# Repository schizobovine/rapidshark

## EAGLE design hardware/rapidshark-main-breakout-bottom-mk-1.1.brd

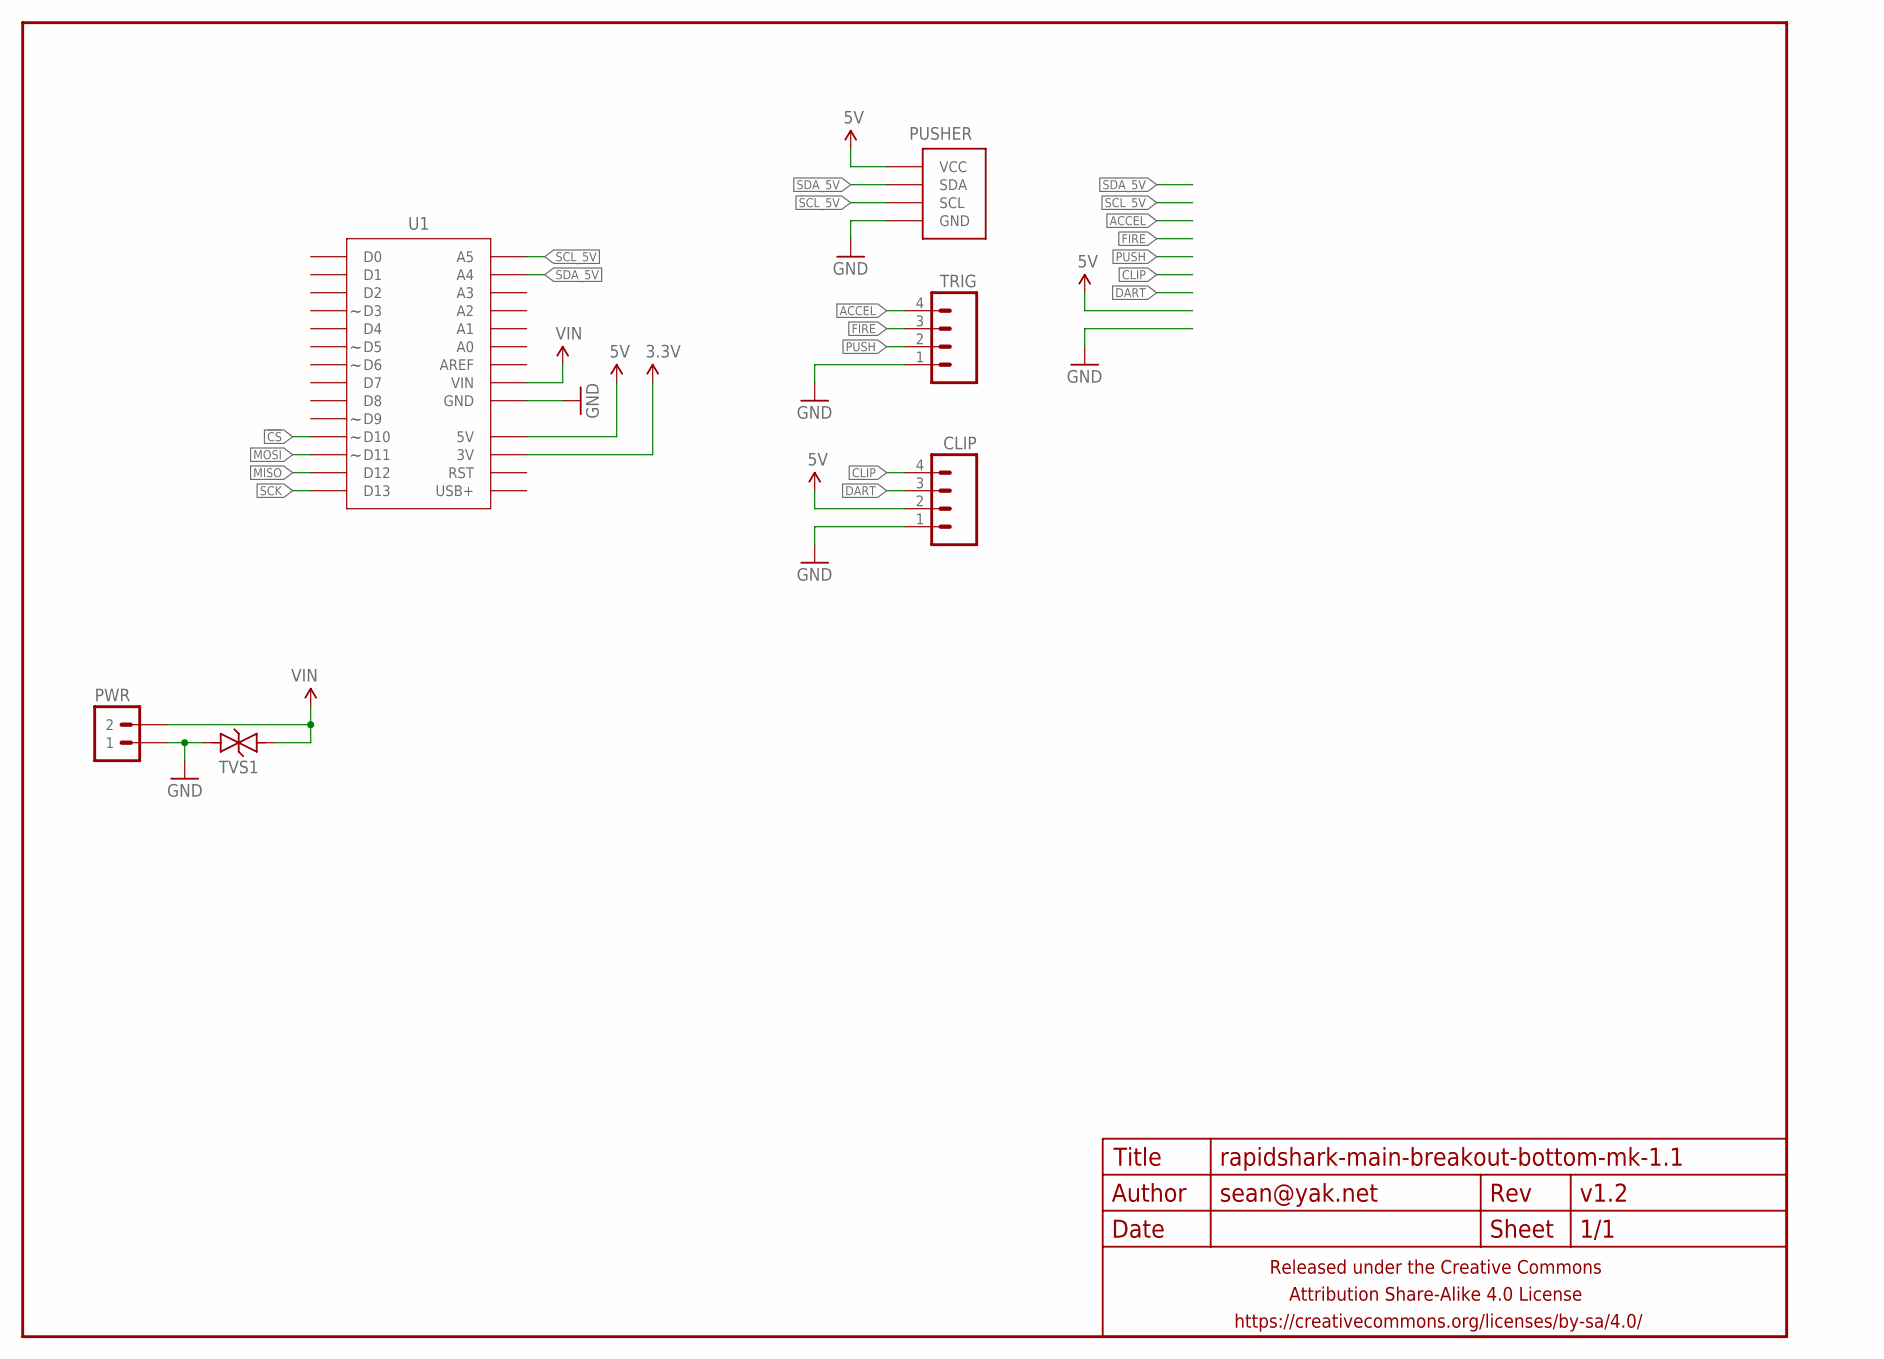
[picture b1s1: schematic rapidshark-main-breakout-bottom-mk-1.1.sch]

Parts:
CLIP: M04JST-PTH-VERT; JST-4-PH-VERT-PTH
FRAME1: FRAME-LETTERNO_PACKAGE; DUMMY
PUSHER: M04-I2CJST-4-PH-VERT-NS; JST-4-PH-VERT-PTH
PWR: M02PTH-CENTERED-R+; 1X02-CENTER-R+
TRIG: M04JST-PTH-VERT; JST-4-PH-VERT-PTH
TVS1: TVSDO-41-10.16MM; DO-41-TVS-BI-10.16MM
U1: ADAFRUIT_METRO_MININOHOLES-OUTSIDER; ADAFRUIT_METRO_MINI_OUTSIDER

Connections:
3.3V: U1.17 (3V)
5V: CLIP.2, PUSHER.2 (VCC), U1.18 (5V)
!CS: U1.11 (D10)
ACCEL: TRIG.4
CLIP: CLIP.4
DART: CLIP.3
FIRE: TRIG.3
GND: CLIP.1, PUSHER.1 (GND), PWR.1, TRIG.1, TVS1.P$1 (1), U1.19 (GND), U1.20 (GND)
MISO: U1.13 (D12)
MOSI: U1.12 (D11)
PUSH: TRIG.2
SCK: U1.14 (D13)
SCL_5V: PUSHER.4 (SCL), U1.28 (A5)
SDA_5V: PUSHER.3 (SDA), U1.27 (A4)
VIN: PWR.2, TVS1.P$2 (2), U1.21 (VIN)

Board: 2 copper layers, 7 parts (2 on the bottom side), 5 nets, no tracks yet.

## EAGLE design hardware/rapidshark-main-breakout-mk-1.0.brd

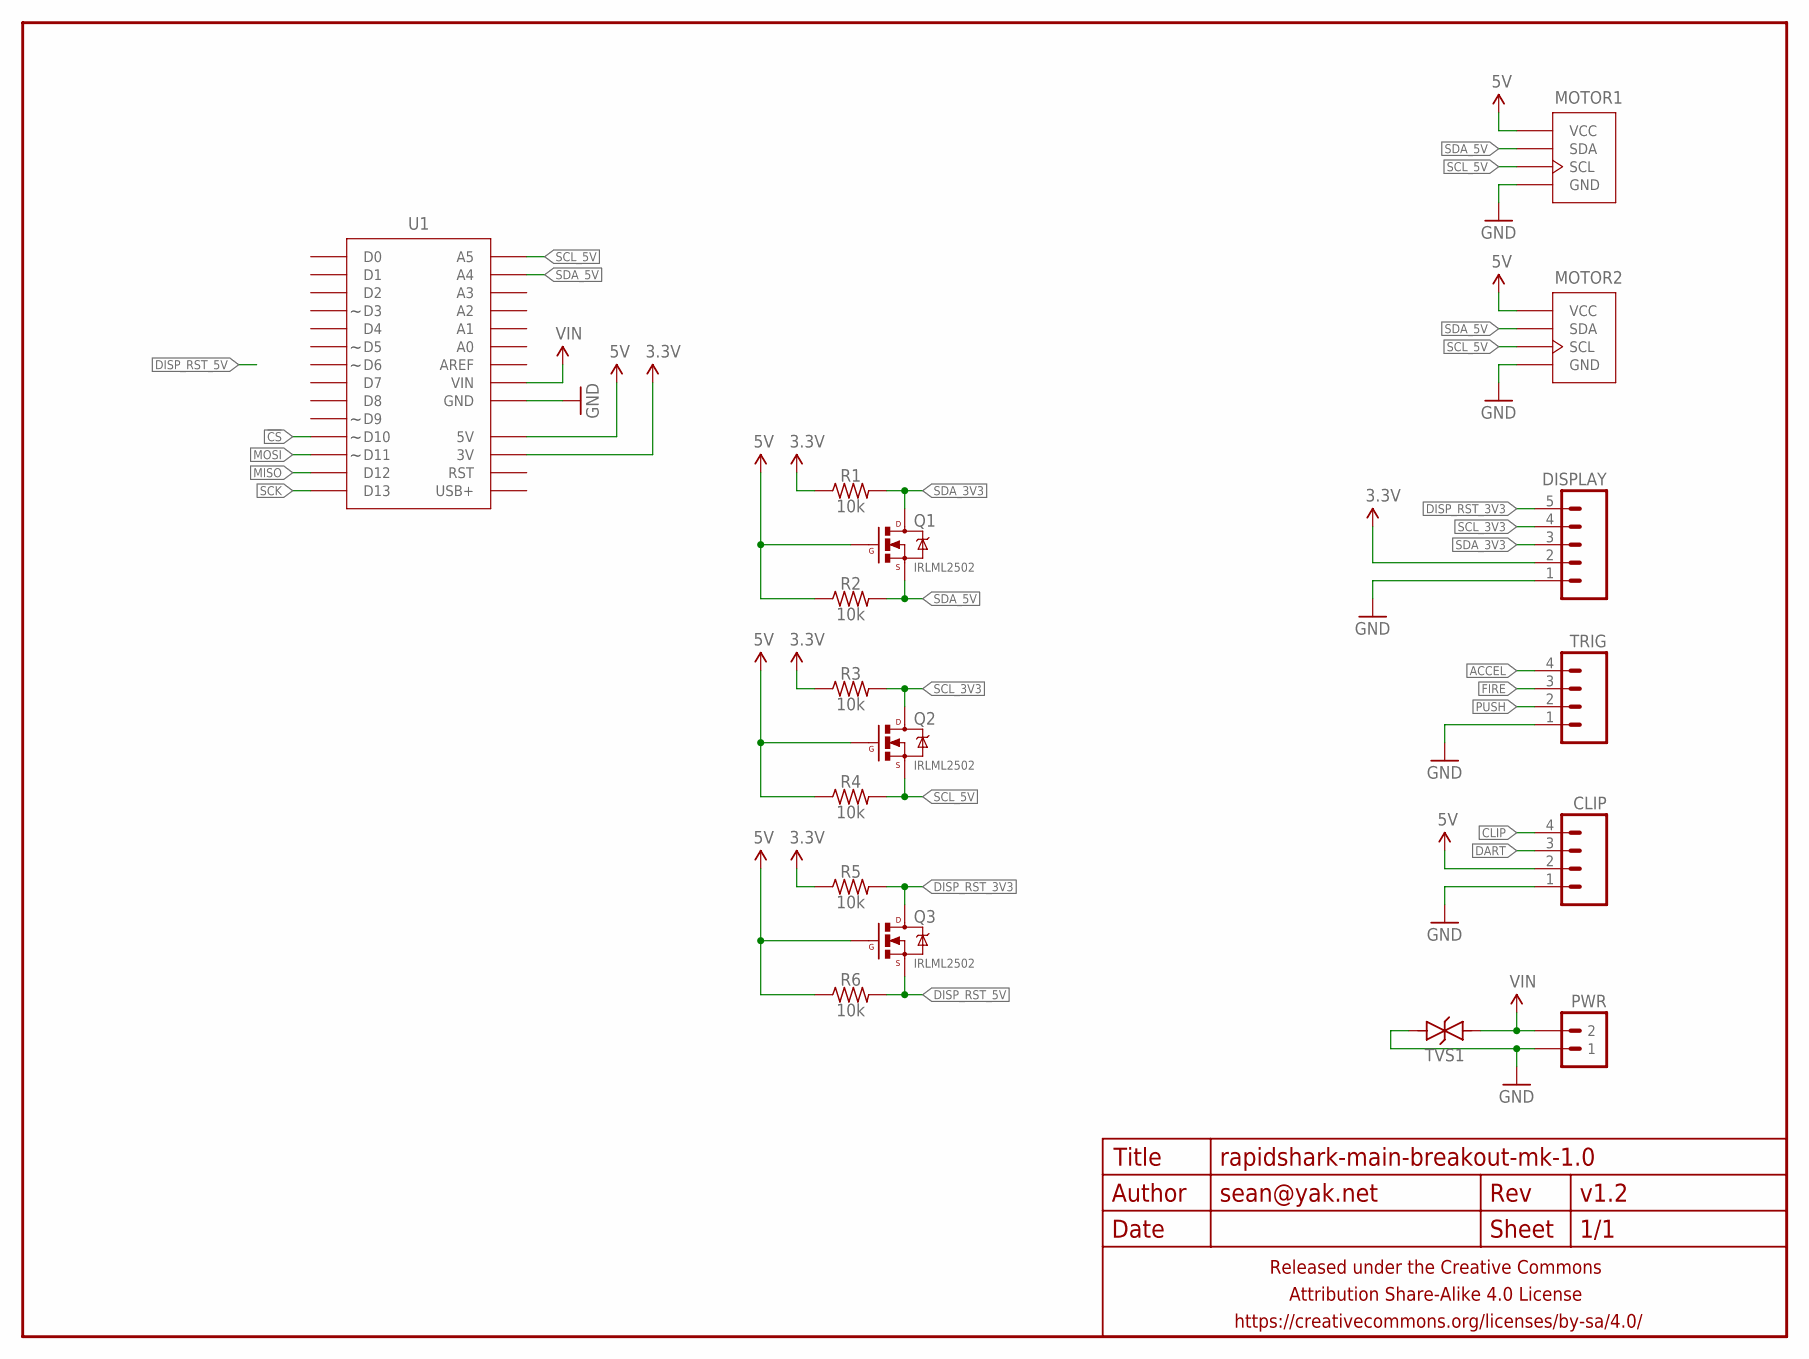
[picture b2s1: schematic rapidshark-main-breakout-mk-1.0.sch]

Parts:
CLIP: M04JST-PTH-VERT; JST-4-PH-VERT-PTH
DISPLAY: M05JST-PH-VERT-PTH; JST-5-PH-VERT-PTH
FRAME1: FRAME-LETTERNO_PACKAGE; DUMMY
MOTOR1, MOTOR2: M04-I2CJST-4-PH-VERT-NS; JST-4-PH-VERT-PTH
PWR: M02PTH-CENTERED-R+; 1X02-CENTER-R+
Q1, Q2, Q3: IRLML2502; SOT23
R1, R2, R3, R4, R5, R6: 10k; R0603
TRIG: M04JST-PTH-VERT; JST-4-PH-VERT-PTH
TVS1: TVSSMA; SMA-DIODE-TVS-BIDIR
U1: ADAFRUIT_METRO_MINISMD-NOHOLES; ADAFRUIT_METRO_MINI_SMD

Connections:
3.3V: DISPLAY.2, R1.1, R3.1, R5.1, U1.17 (3V)
5V: CLIP.2, MOTOR1.2 (VCC), MOTOR2.2 (VCC), Q1.1 (G), Q2.1 (G), Q3.1 (G), R2.1, R4.1, R6.1, U1.18 (5V)
!CS: U1.11 (D10)
ACCEL: TRIG.4
CLIP: CLIP.4
DART: CLIP.3
DISP_RST_3V3: DISPLAY.5, Q3.3 (D), R5.2
DISP_RST_5V: Q3.2 (S), R6.2
FIRE: TRIG.3
GND: CLIP.1, DISPLAY.1, MOTOR1.1 (GND), MOTOR2.1 (GND), PWR.1, TRIG.1, TVS1.2, U1.19 (GND), U1.20 (GND)
MISO: U1.13 (D12)
MOSI: U1.12 (D11)
PUSH: TRIG.2
SCK: U1.14 (D13)
SCL_3V3: DISPLAY.4, Q2.3 (D), R3.2
SCL_5V: MOTOR1.4 (SCL), MOTOR2.4 (SCL), Q2.2 (S), R4.2, U1.28 (A5)
SDA_3V3: DISPLAY.3, Q1.3 (D), R1.2
SDA_5V: MOTOR1.3 (SDA), MOTOR2.3 (SDA), Q1.2 (S), R2.2, U1.27 (A4)
VIN: PWR.2, TVS1.1, U1.21 (VIN)

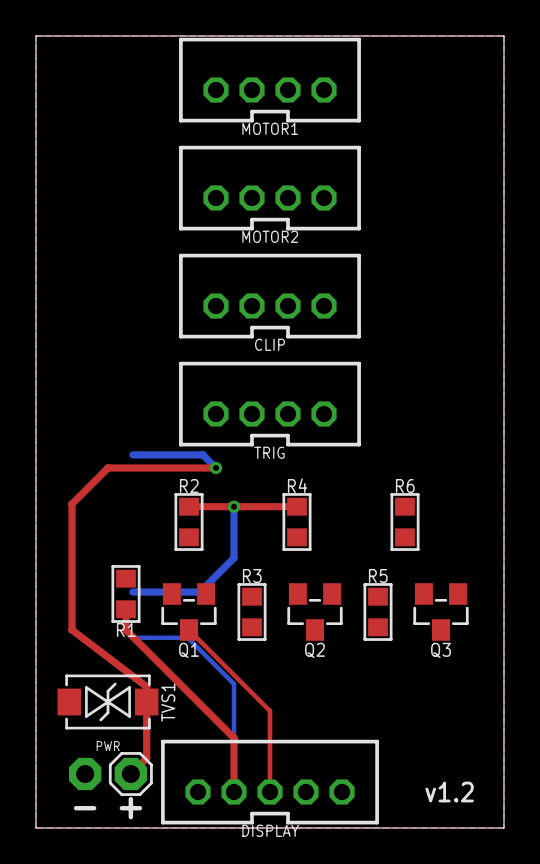
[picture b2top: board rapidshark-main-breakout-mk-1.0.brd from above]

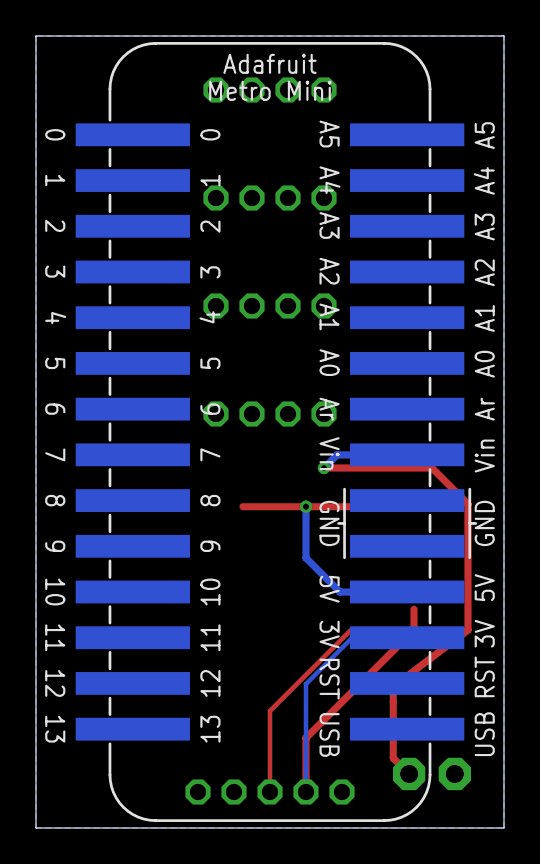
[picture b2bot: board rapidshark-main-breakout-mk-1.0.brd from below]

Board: 2 copper layers, 26.0 x 44.0 mm, 18 parts (2 on the bottom side), 10 nets.

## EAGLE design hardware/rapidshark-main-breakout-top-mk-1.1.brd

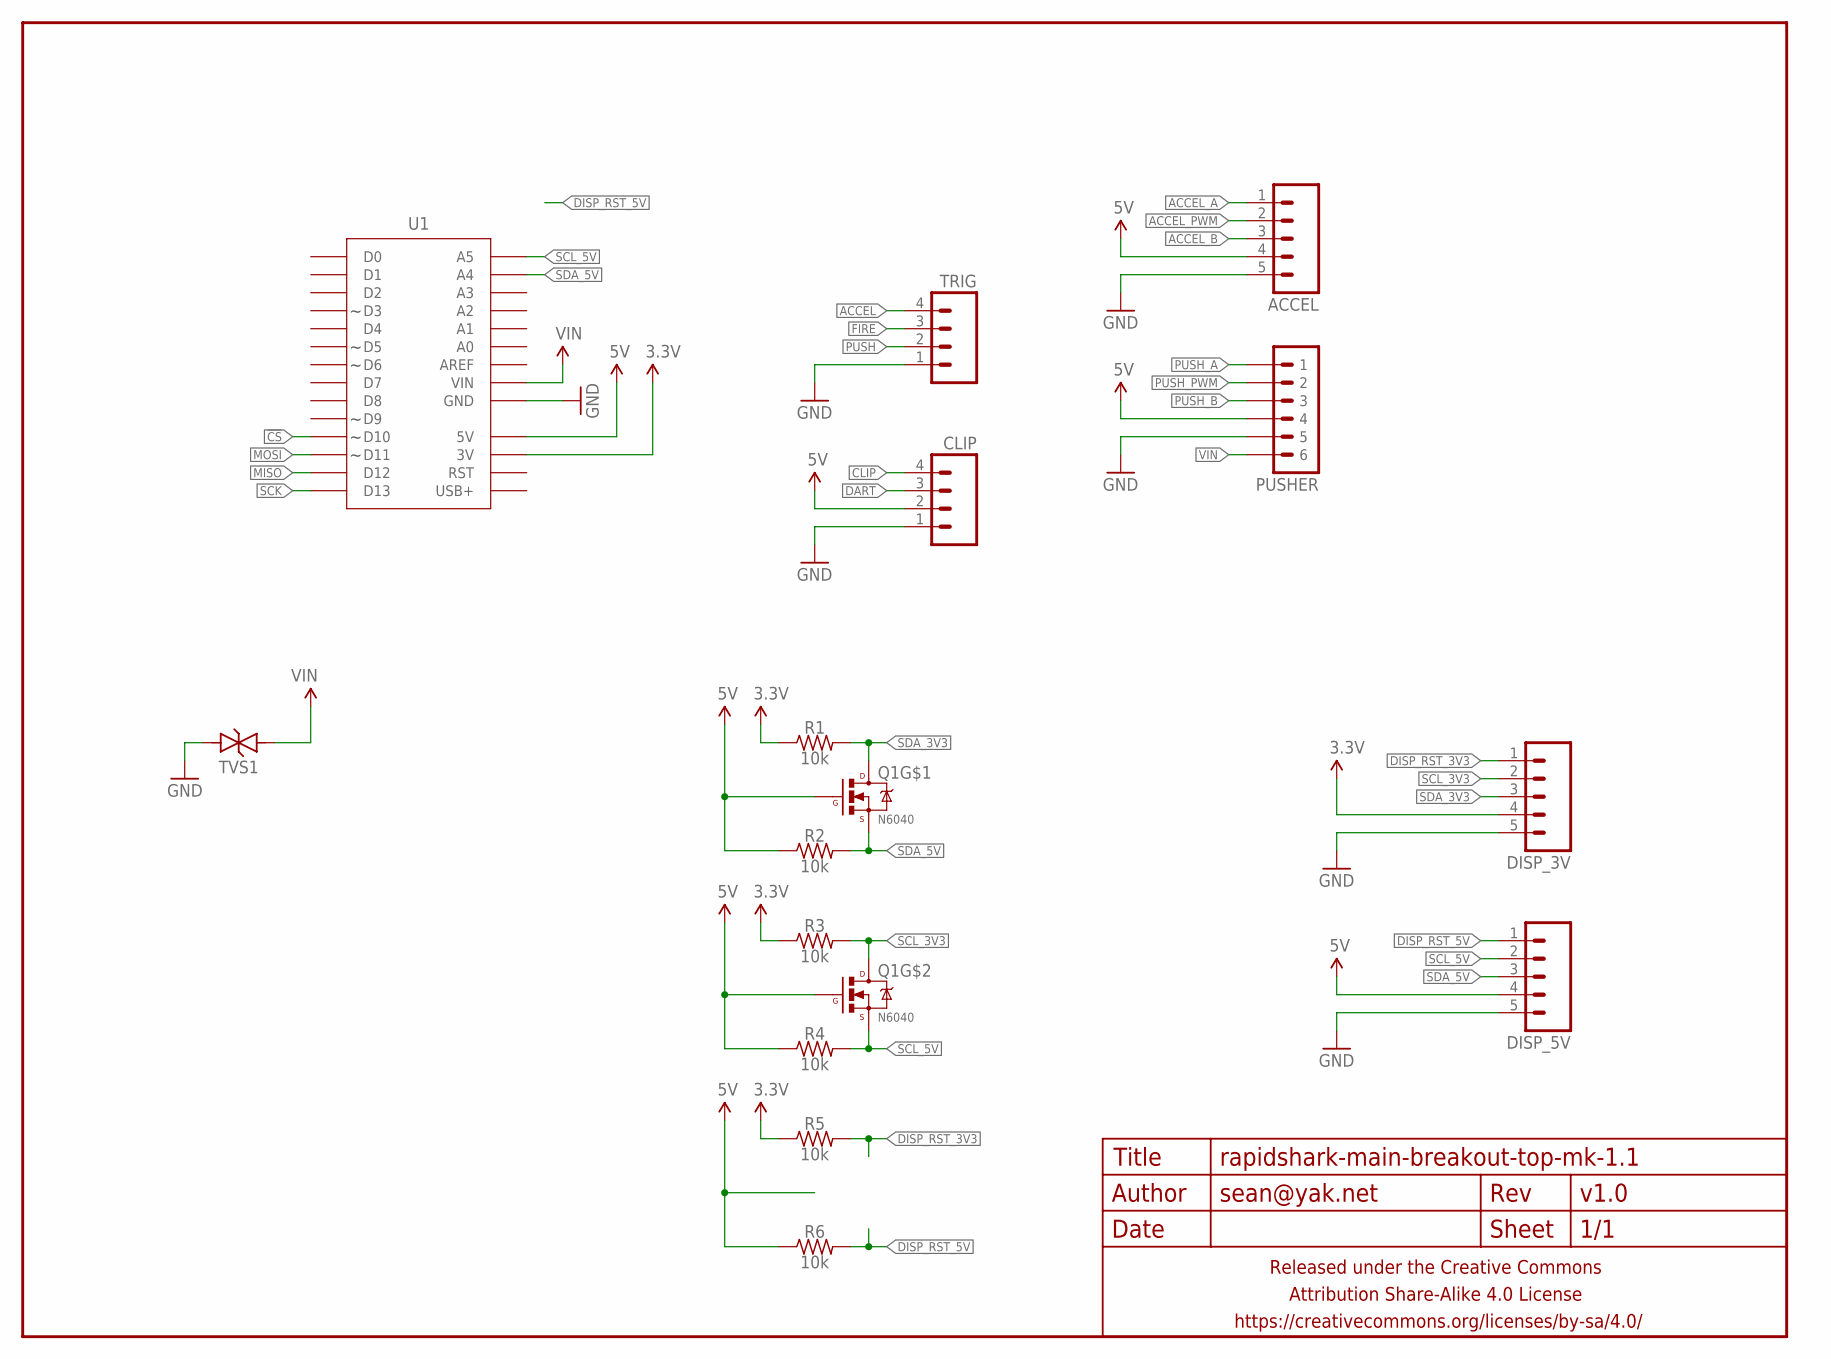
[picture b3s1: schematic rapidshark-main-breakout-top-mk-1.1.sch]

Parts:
ACCEL: M05JST-PH-VERT-PTH; JST-5-PH-VERT-PTH
CLIP: M04JST-PTH-VERT; JST-4-PH-VERT-PTH
DISP_3V, DISP_5V: M05JST-PH-VERT-PTH; JST-5-PH-VERT-PTH
FRAME1: FRAME-LETTERNO_PACKAGE; DUMMY
PUSHER: M06JST-PH-PTH-VERT; JST-6-PH-VERT-PTH
Q1: N6040; SO08
R1, R2, R3, R4, R5, R6: 10k; R0603
TRIG: M04JST-PTH-VERT; JST-4-PH-VERT-PTH
TVS1: TVSSMA; SMA-DIODE-TVS-BIDIR
U1: ADAFRUIT_METRO_MININOSILK-ABMBI; ADAFRUIT_METRO_MINI_FLIPPED

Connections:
3.3V: DISP_3V.4, R1.1, R3.1, R5.1, U1.17 (3V)
5V: ACCEL.4, CLIP.2, DISP_5V.4, Q1.2 (G), Q1.4 (G), R2.1, R4.1, R6.1, U1.18 (5V)
!CS: U1.11 (D10)
ACCEL: TRIG.4
ACCEL_A: ACCEL.1
ACCEL_B: ACCEL.3
ACCEL_PWM: ACCEL.2
CLIP: CLIP.4
DART: CLIP.3
DISP_RST_3V3: DISP_3V.1, R5.2
DISP_RST_5V: DISP_5V.1, R6.2
FIRE: TRIG.3
GND: ACCEL.5, CLIP.1, DISP_3V.5, DISP_5V.5, TRIG.1, TVS1.1, U1.19 (GND), U1.20 (GND)
MISO: U1.13 (D12)
MOSI: U1.12 (D11)
PUSH: TRIG.2
PUSH_A: PUSHER.1
PUSH_B: PUSHER.3
PUSH_PWM: PUSHER.2
SCK: U1.14 (D13)
SCL_3V3: DISP_3V.2, Q1.5 (D), Q1.6 (D), R3.2
SCL_5V: DISP_5V.2, Q1.3 (S), R4.2, U1.28 (A5)
SDA_3V3: DISP_3V.3, Q1.7 (D), Q1.8 (D), R1.2
SDA_5V: DISP_5V.3, Q1.1 (S), R2.2, U1.27 (A4)
VIN: PUSHER.6, TVS1.2, U1.21 (VIN)

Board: 2 copper layers, 16 parts (1 on the bottom side), 10 nets, no tracks yet.

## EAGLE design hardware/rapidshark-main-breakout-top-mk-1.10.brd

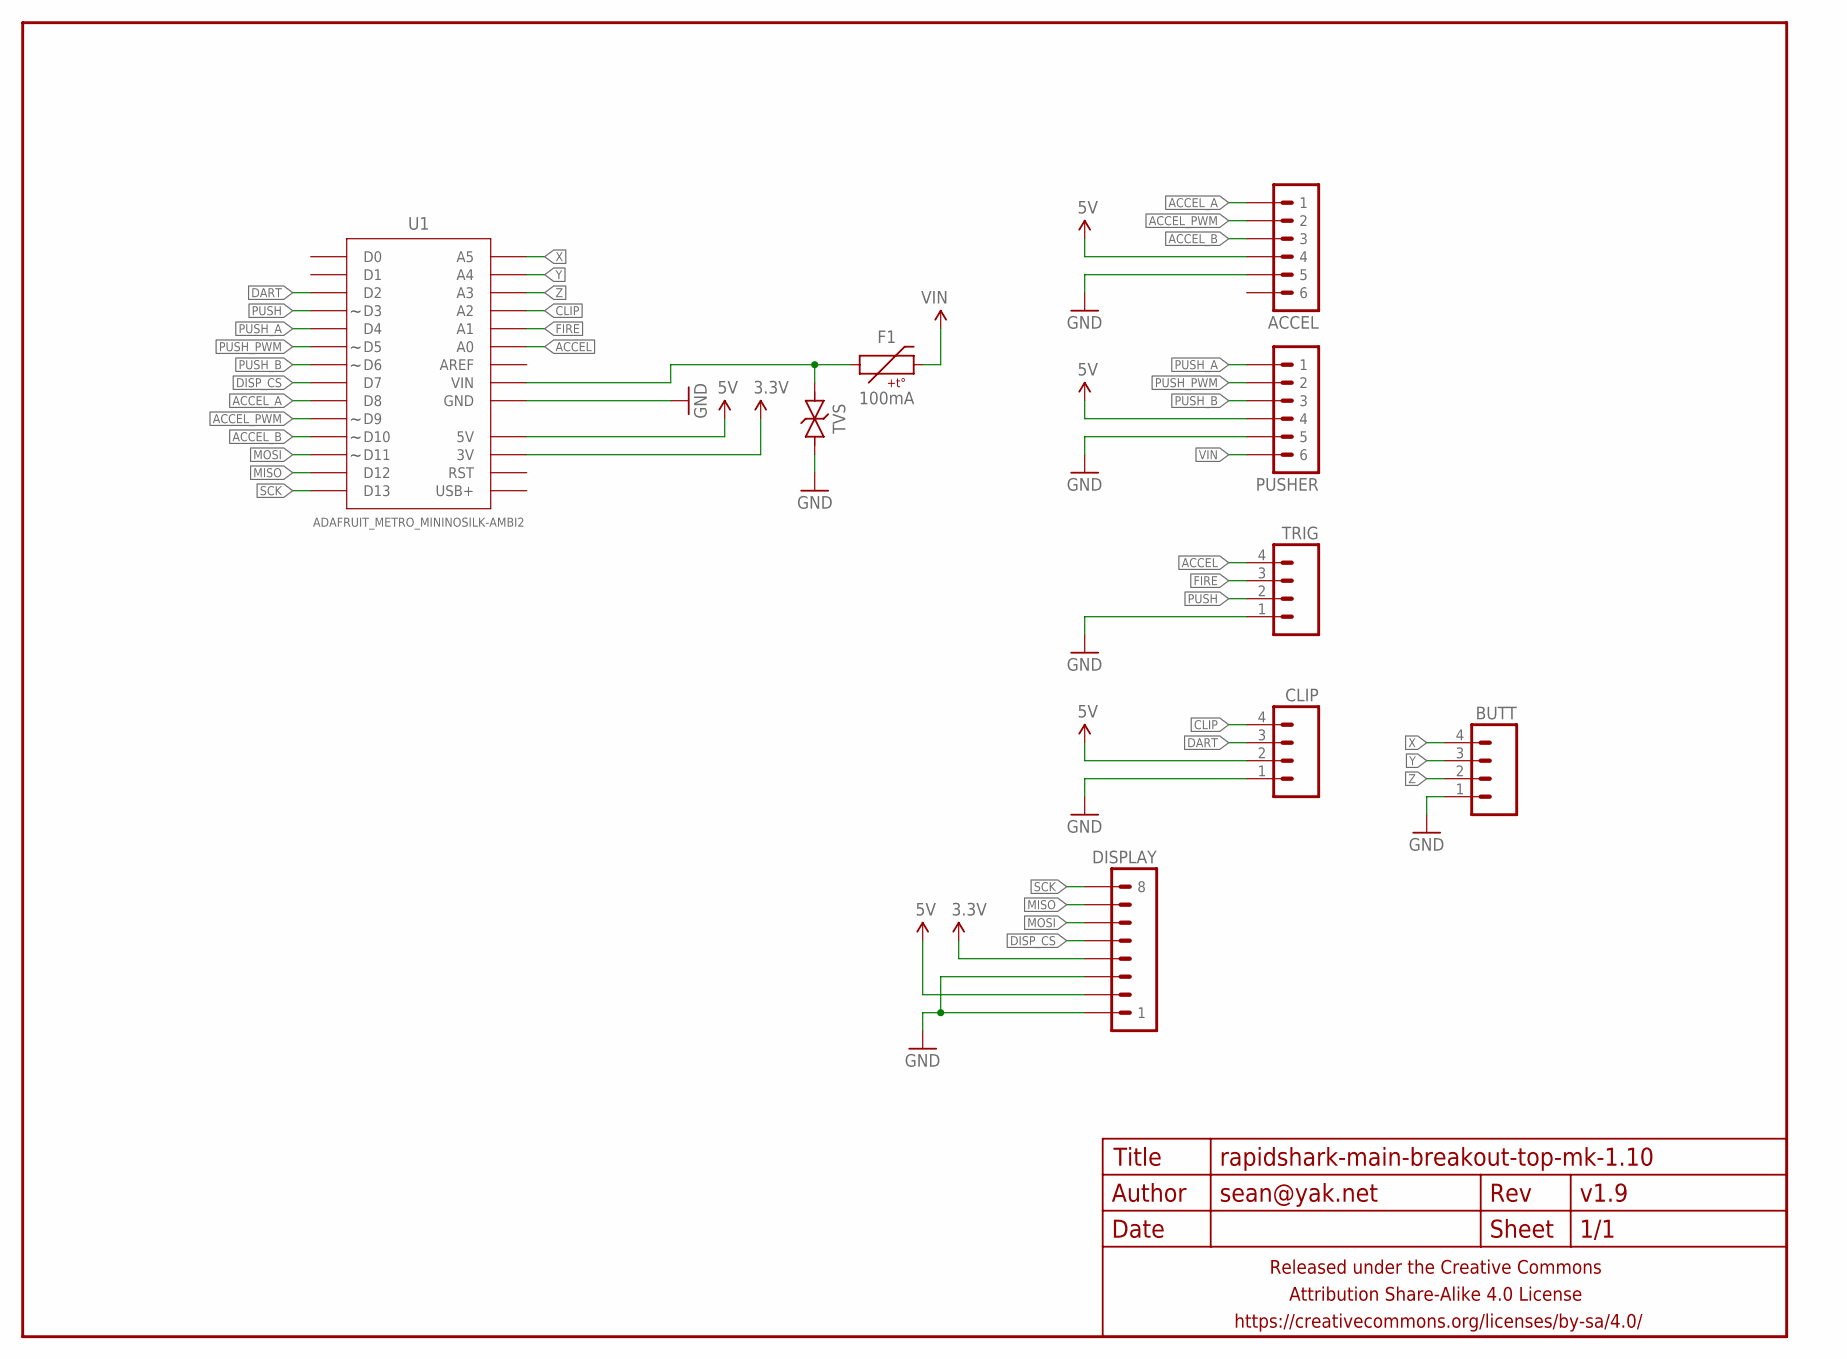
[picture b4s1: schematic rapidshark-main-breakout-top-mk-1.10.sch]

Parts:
ACCEL: M06JST-PH-PTH-VERT; JST-6-PH-VERT-PTH
BUTT: M04JST-PTH-VERT; JST-4-PH-VERT-PTH
CLIP: M04JST-PTH-VERT; JST-4-PH-VERT-PTH
DISPLAY: M08JST-PH-VERT-PTH; JST-8-VERT-PTH
F1: 100mA; PTC-1206
FRAME1: FRAME-LETTERNO_PACKAGE; DUMMY
PUSHER: M06JST-PH-PTH-VERT; JST-6-PH-VERT-PTH
TRIG: M04JST-PTH-VERT; JST-4-PH-VERT-PTH
TVS: TVSSMA; SMA-DIODE-TVS-BIDIR
U1: ADAFRUIT_METRO_MININOSILK-AMBI2; ADAFRUIT_METRO_MINI_BACK

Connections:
3.3V: DISPLAY.4, U1.17 (3V)
5V: ACCEL.4, CLIP.2, DISPLAY.2, PUSHER.4, U1.18 (5V)
ACCEL: TRIG.4, U1.23 (A0)
ACCEL_A: ACCEL.1, U1.9 (D8)
ACCEL_B: ACCEL.3, U1.11 (D10)
ACCEL_PWM: ACCEL.2, U1.10 (D9)
CLIP: CLIP.4, U1.25 (A2)
DART: CLIP.3, U1.3 (D2)
DISP_CS: DISPLAY.5, U1.8 (D7)
FIRE: TRIG.3, U1.24 (A1)
GND: ACCEL.5, BUTT.1, CLIP.1, DISPLAY.1, DISPLAY.3, PUSHER.5, TRIG.1, TVS.1, U1.19 (GND), U1.20 (GND)
MISO: DISPLAY.7, U1.13 (D12)
MOSI: DISPLAY.6, U1.12 (D11)
unnamed: F1.1, TVS.2, U1.21 (VIN)
PUSH: TRIG.2, U1.4 (D3)
PUSH_A: PUSHER.1, U1.5 (D4)
PUSH_B: PUSHER.3, U1.7 (D6)
PUSH_PWM: PUSHER.2, U1.6 (D5)
SCK: DISPLAY.8, U1.14 (D13)
VIN: F1.2, PUSHER.6
X: BUTT.4, U1.28 (A5)
Y: BUTT.3, U1.27 (A4)
Z: BUTT.2, U1.26 (A3)

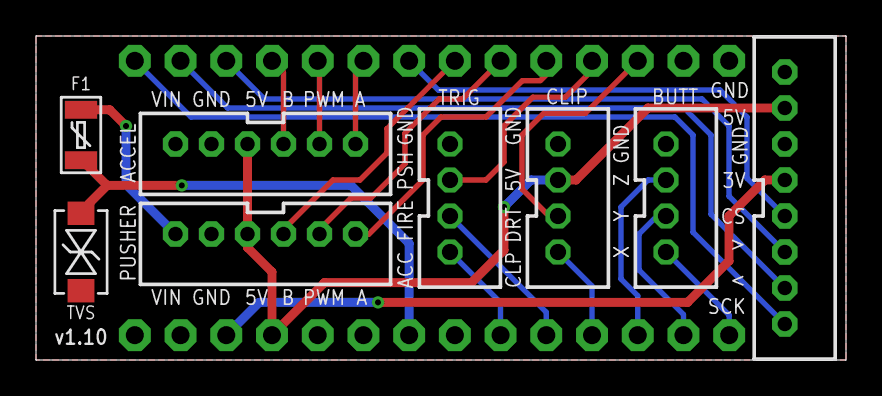
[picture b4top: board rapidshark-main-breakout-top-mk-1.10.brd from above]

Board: 2 copper layers, 45.0 x 18.0 mm, 10 parts (1 on the bottom side), 23 nets.

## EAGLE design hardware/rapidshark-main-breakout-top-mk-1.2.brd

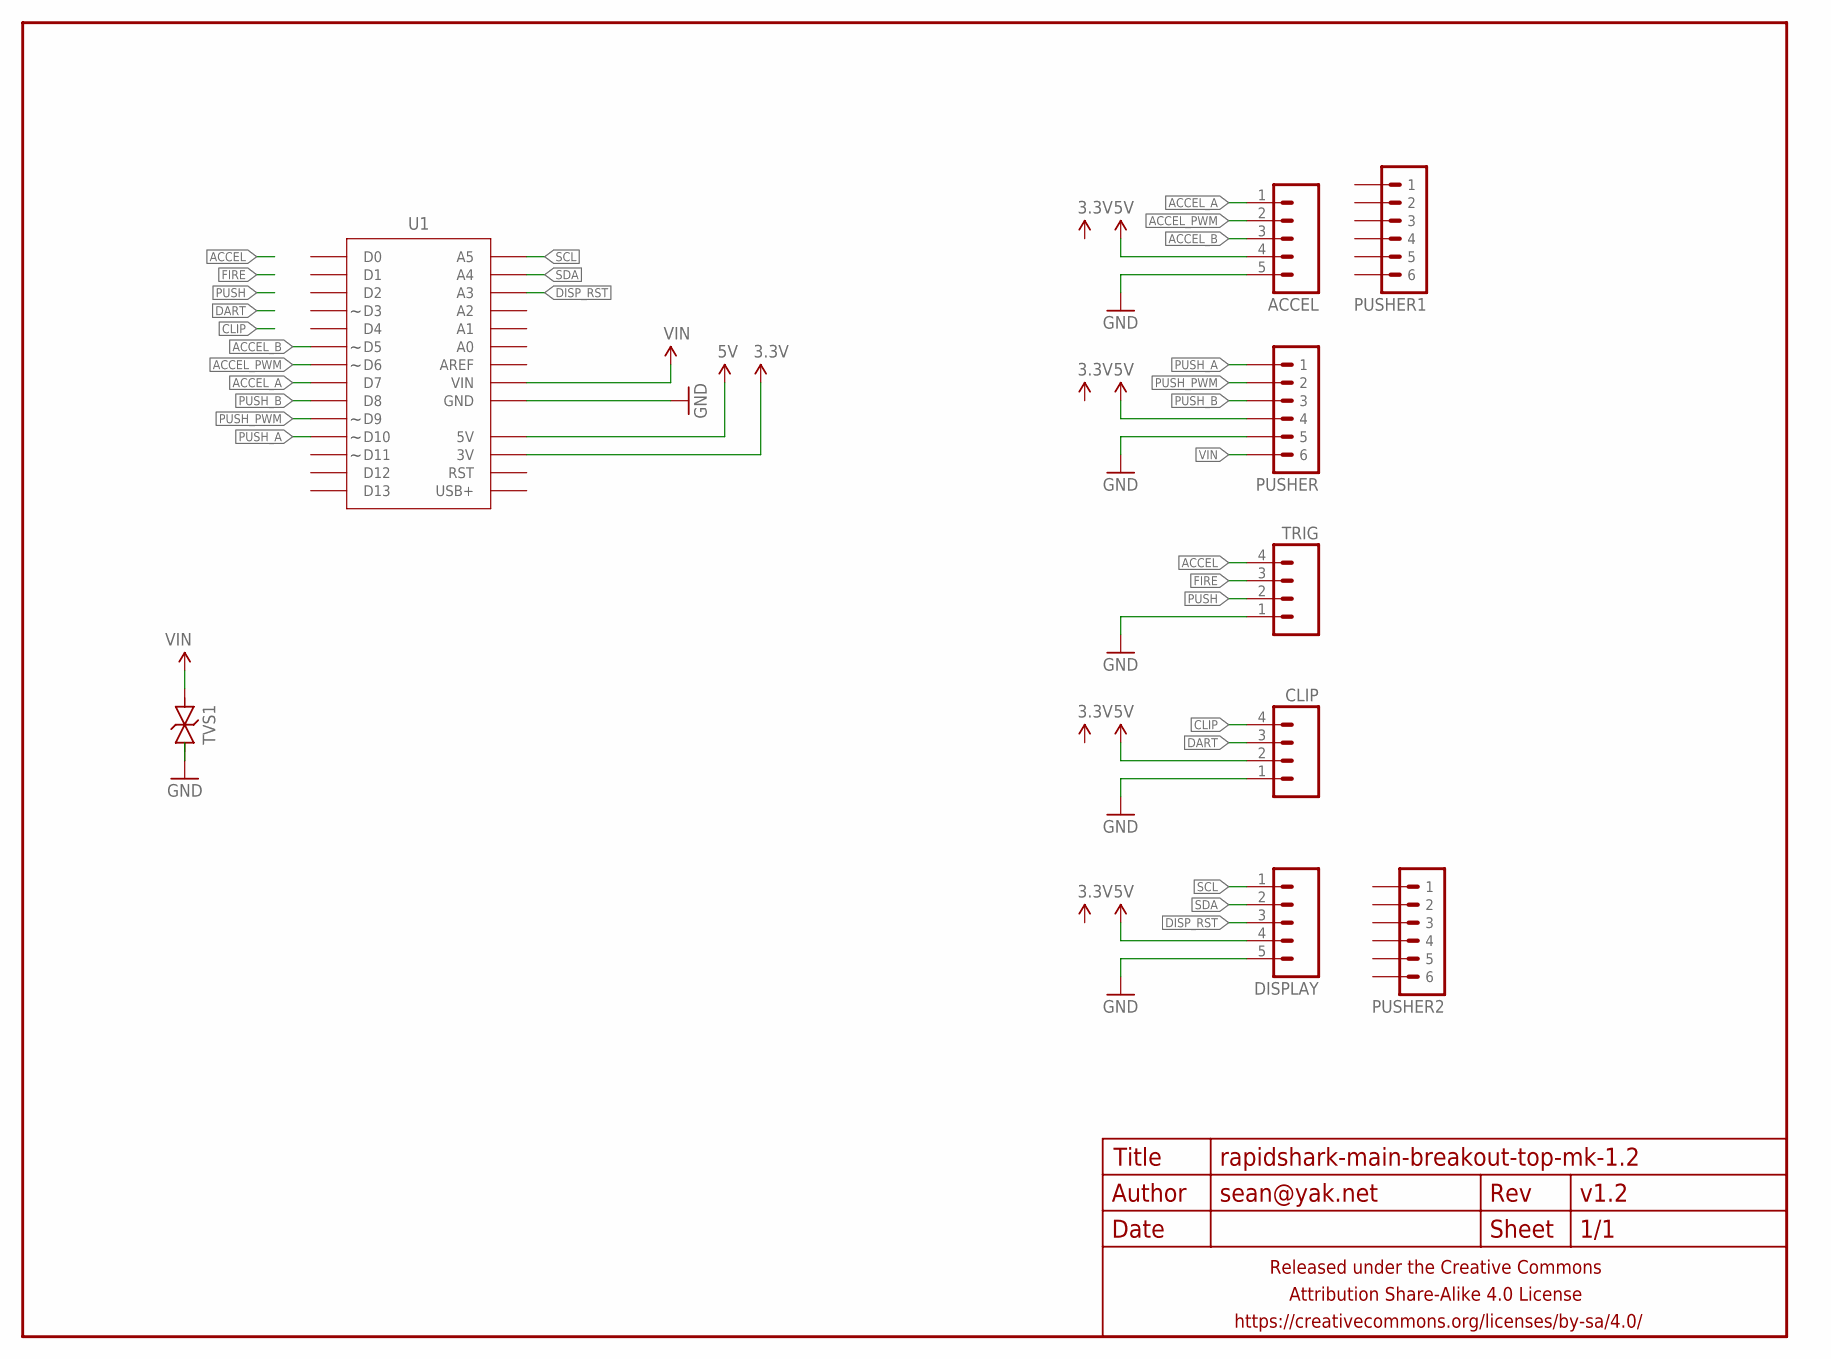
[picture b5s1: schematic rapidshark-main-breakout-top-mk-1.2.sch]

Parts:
ACCEL: M05JST-PH-VERT-PTH; JST-5-PH-VERT-PTH
CLIP: M04JST-PTH-VERT; JST-4-PH-VERT-PTH
DISPLAY: M05JST-PH-VERT-PTH; JST-5-PH-VERT-PTH
FRAME1: FRAME-LETTERNO_PACKAGE; DUMMY
PUSHER, PUSHER1, PUSHER2: M06JST-PH-PTH-VERT; JST-6-PH-VERT-PTH
TRIG: M04JST-PTH-VERT; JST-4-PH-VERT-PTH
TVS1: TVSDO-41-8.89MM; DO-41-TVS-BI-8.89MM
U1: ADAFRUIT_METRO_MININOSILK-ABMBI; ADAFRUIT_METRO_MINI_FLIPPED

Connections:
3.3V: U1.17 (3V)
5V: ACCEL.4, CLIP.2, DISPLAY.4, PUSHER.4, U1.18 (5V)
ACCEL: TRIG.4
ACCEL_A: ACCEL.1, U1.8 (D7)
ACCEL_B: ACCEL.3, U1.6 (D5)
ACCEL_PWM: ACCEL.2, U1.7 (D6)
CLIP: CLIP.4
DART: CLIP.3
DISP_RST: DISPLAY.3, U1.26 (A3)
FIRE: TRIG.3
GND: ACCEL.5, CLIP.1, DISPLAY.5, PUSHER.5, TRIG.1, TVS1.P$1 (1), U1.19 (GND), U1.20 (GND)
PUSH: TRIG.2
PUSH_A: PUSHER.1, U1.11 (D10)
PUSH_B: PUSHER.3, U1.9 (D8)
PUSH_PWM: PUSHER.2, U1.10 (D9)
SCL: DISPLAY.1, U1.28 (A5)
SDA: DISPLAY.2, U1.27 (A4)
VIN: PUSHER.6, TVS1.P$2 (2), U1.21 (VIN)

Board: 2 copper layers, 10 parts (1 on the bottom side), 12 nets, no tracks yet.

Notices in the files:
parts and their libraries:
A_butts: Released under the Creative Commons Attribution Share-Alike 4.0 License
A_butts: https://creativecommons.org/licenses/by-sa/4.0
A_butts: Released under the Creative Commons
